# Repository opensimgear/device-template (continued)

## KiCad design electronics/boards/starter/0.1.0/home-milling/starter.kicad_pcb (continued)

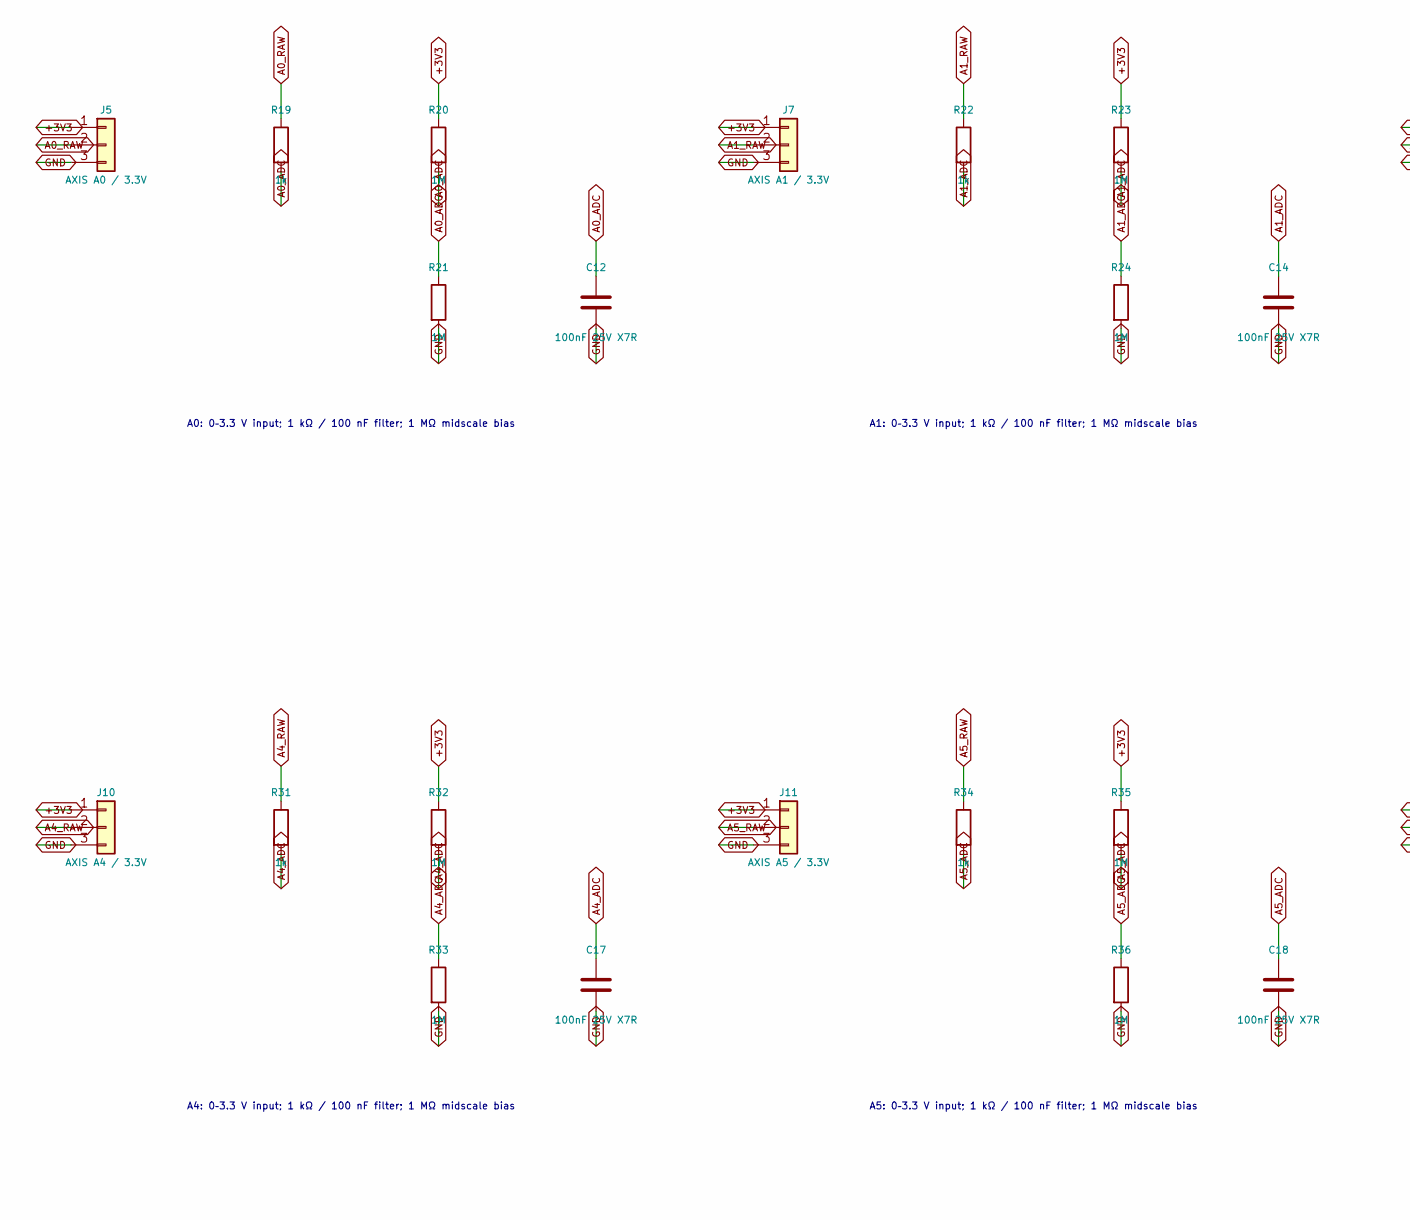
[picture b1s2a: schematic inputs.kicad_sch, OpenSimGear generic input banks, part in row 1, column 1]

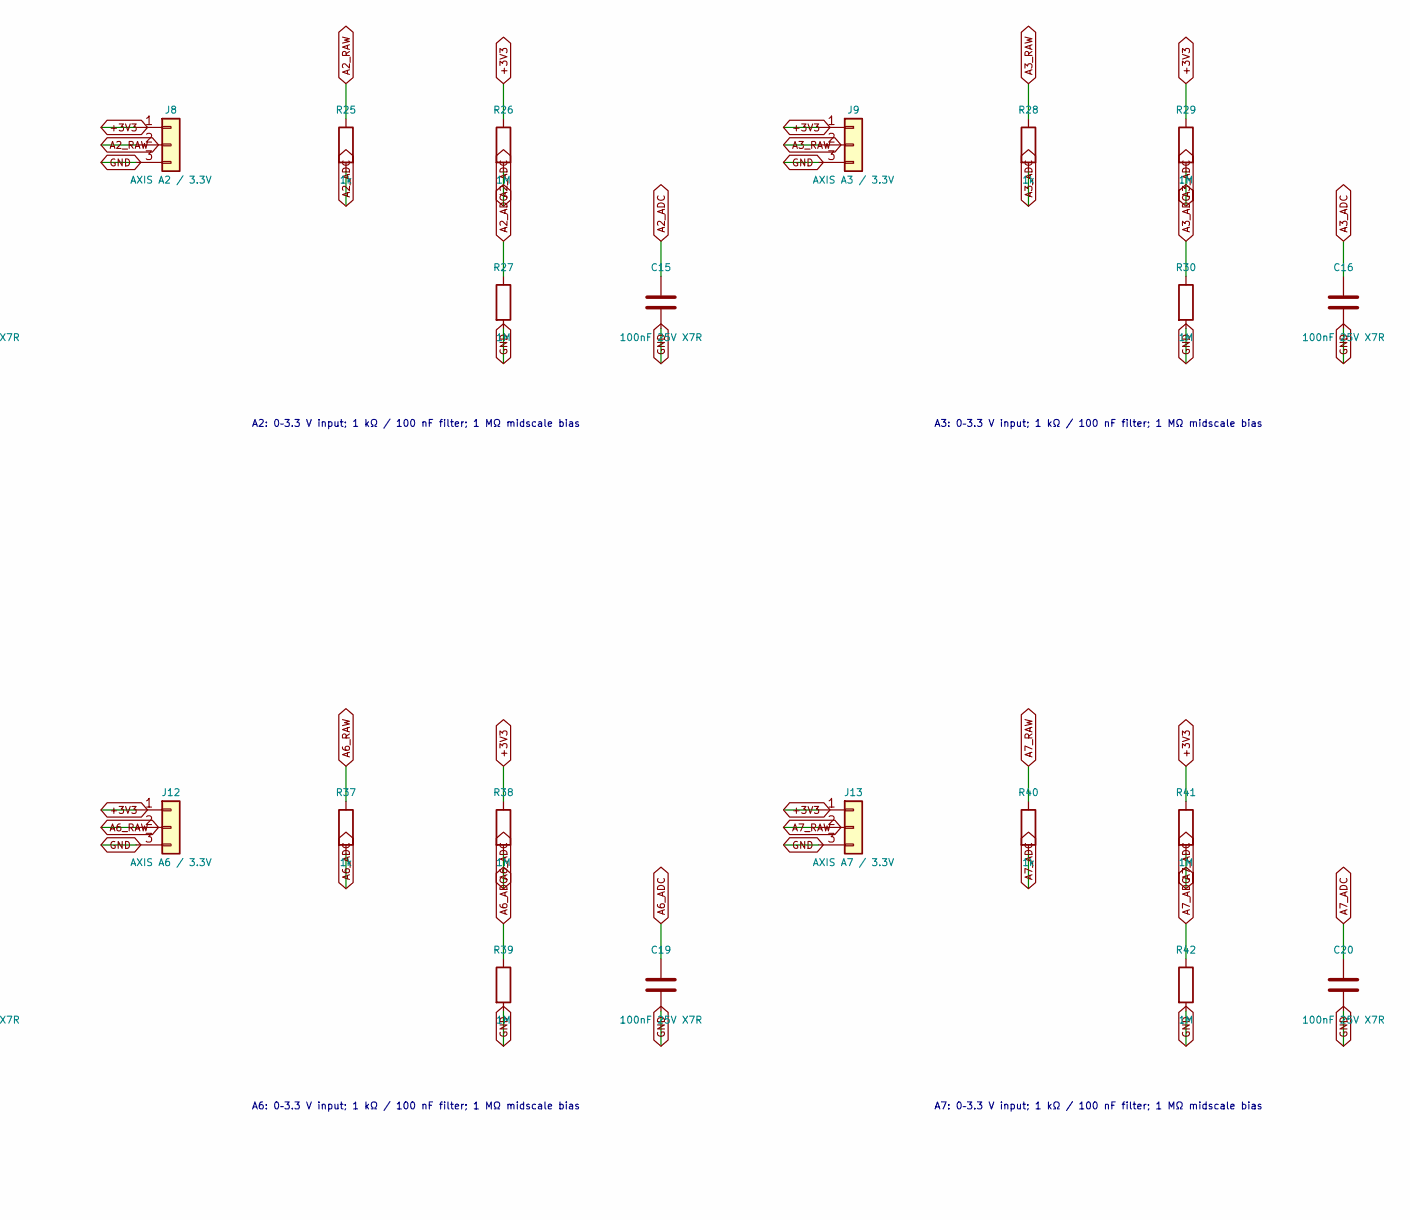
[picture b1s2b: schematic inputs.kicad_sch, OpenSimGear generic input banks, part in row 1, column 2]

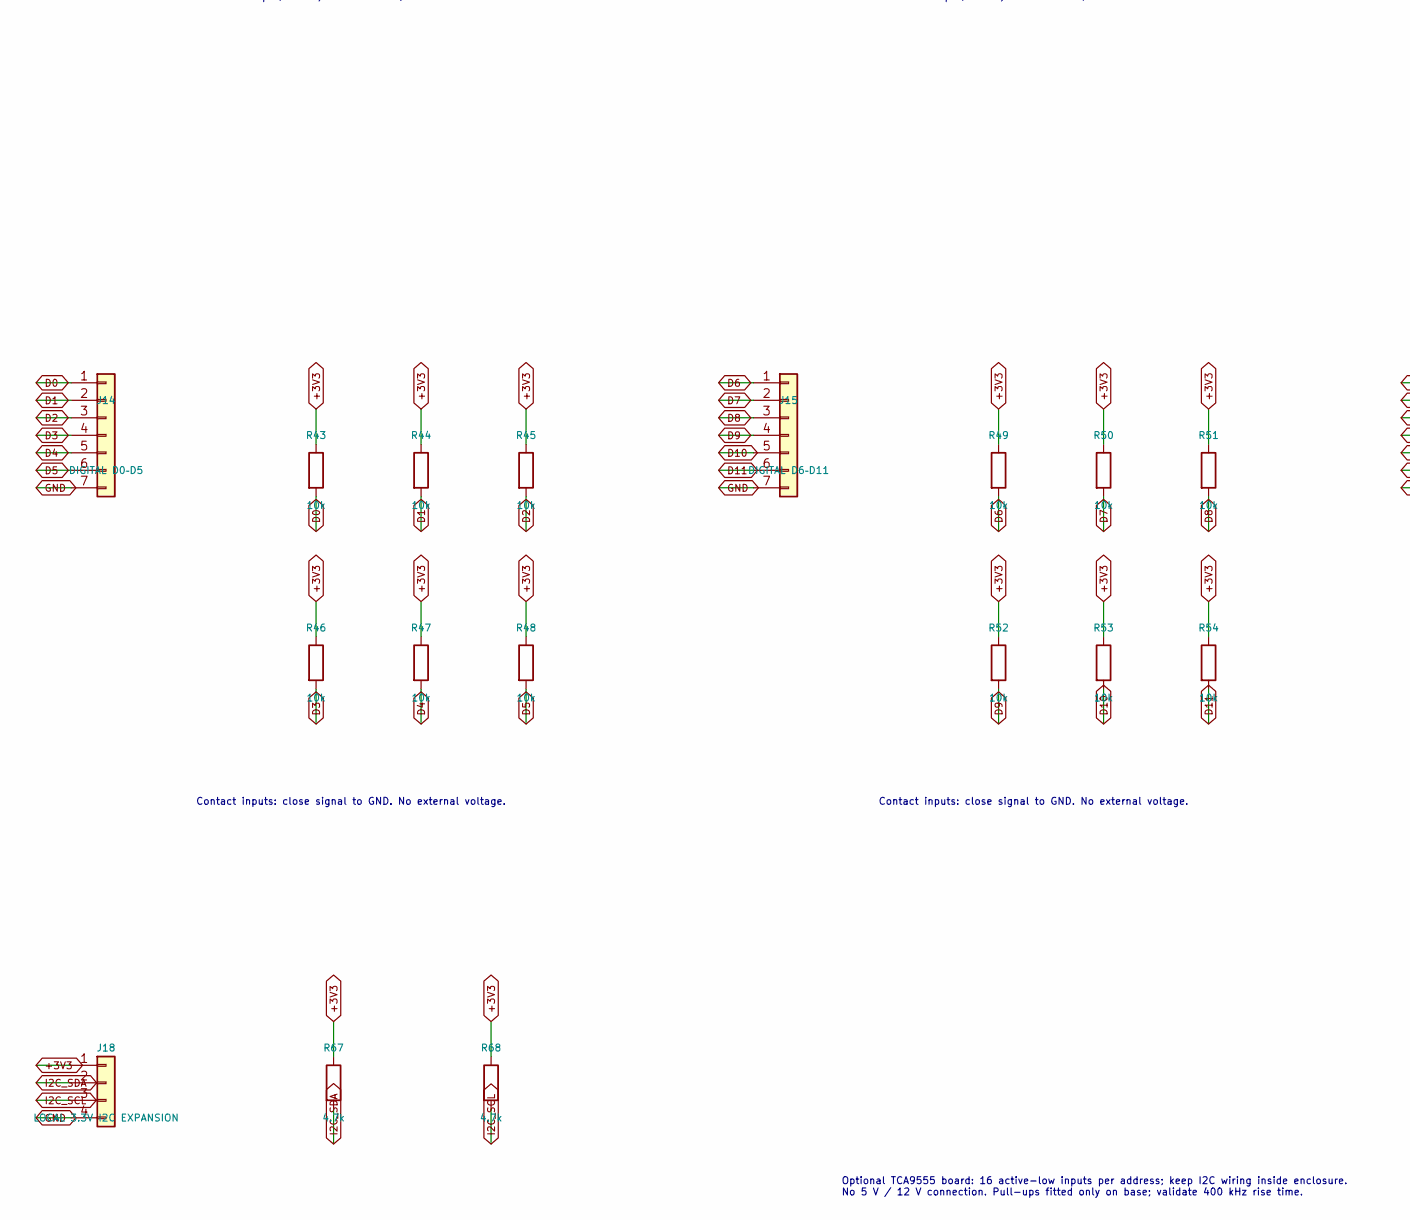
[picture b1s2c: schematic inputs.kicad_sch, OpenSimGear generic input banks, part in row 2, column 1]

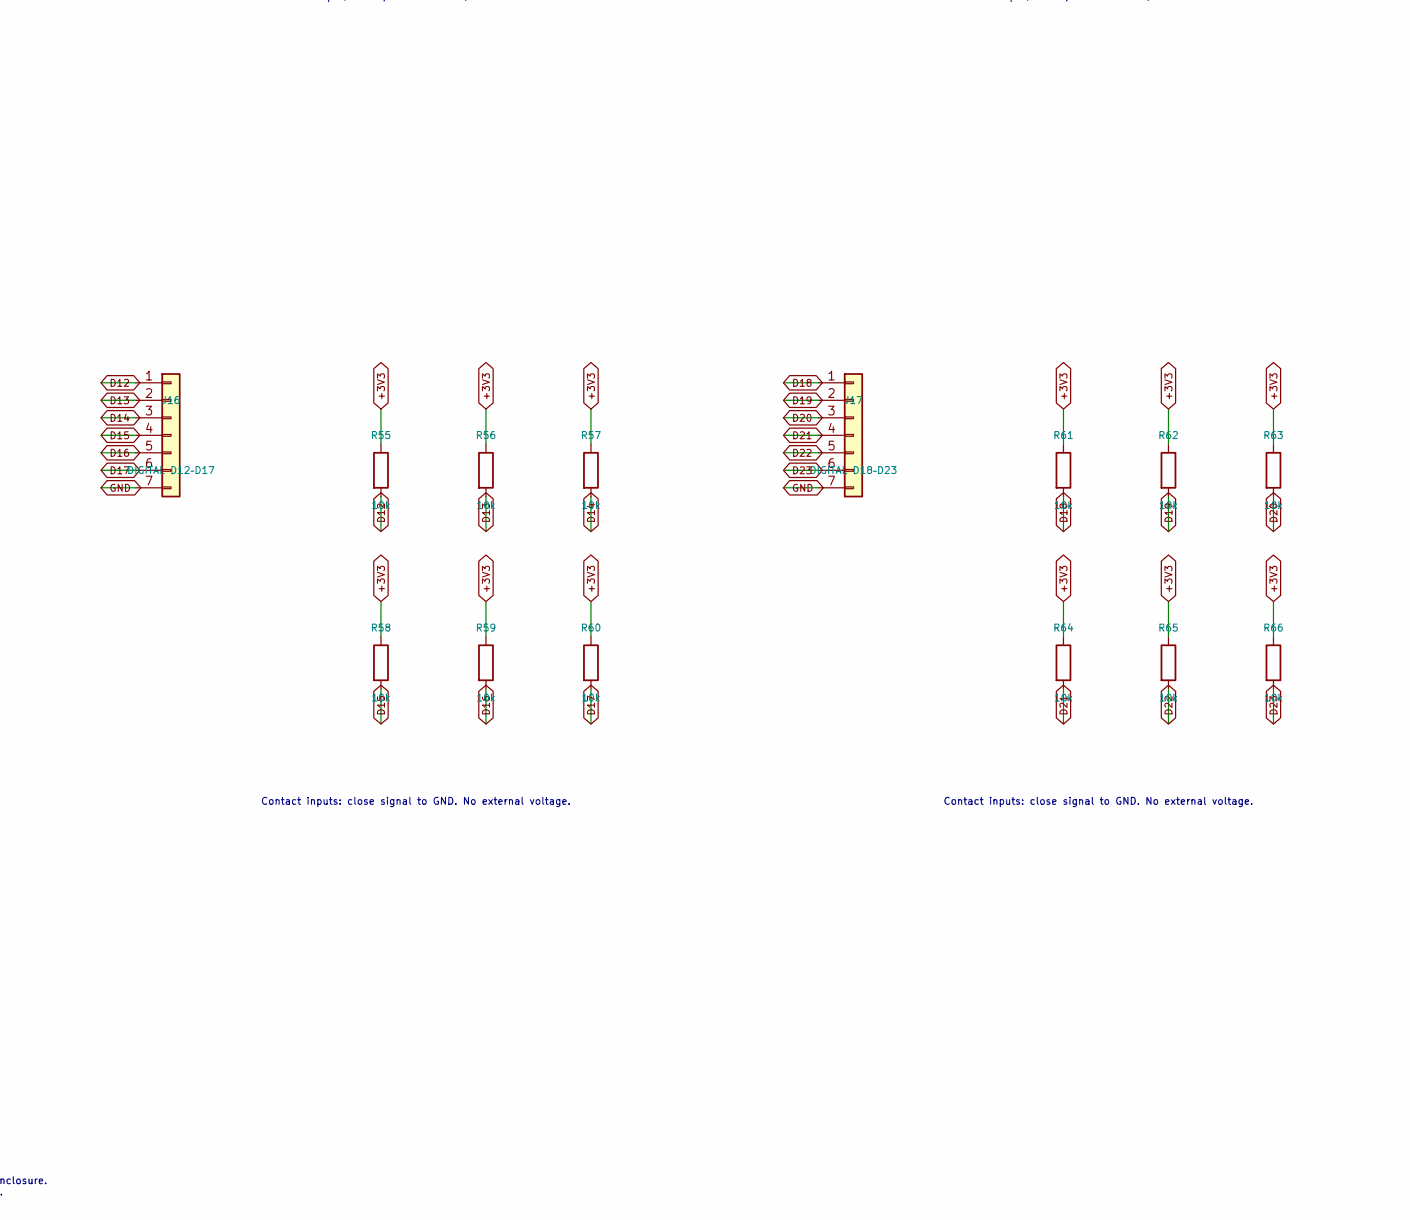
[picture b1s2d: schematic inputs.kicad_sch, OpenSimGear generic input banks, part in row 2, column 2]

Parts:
C12: 100nF 25V X7R; C12_C_0805_2012Metric_HomeMilling; MPN C0805C104K3RACTU
C14: 100nF 25V X7R; C14_C_0805_2012Metric_HomeMilling; MPN C0805C104K3RACTU
C15: 100nF 25V X7R; C15_C_0805_2012Metric_HomeMilling; MPN C0805C104K3RACTU
C16: 100nF 25V X7R; C16_C_0805_2012Metric_HomeMilling; MPN C0805C104K3RACTU
C17: 100nF 25V X7R; C17_C_0805_2012Metric_HomeMilling; MPN C0805C104K3RACTU
C18: 100nF 25V X7R; C18_C_0805_2012Metric_HomeMilling; MPN C0805C104K3RACTU
C19: 100nF 25V X7R; C19_C_0805_2012Metric_HomeMilling; MPN C0805C104K3RACTU
C20: 100nF 25V X7R; C20_C_0805_2012Metric_HomeMilling; MPN C0805C104K3RACTU
J5: AXIS A0 / 3.3V; J5_PinHeader_Samtec_TSW-103-07-L-S_P2.54mm_Vertical_HomeMil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; MPN TSW-103-07-L-S
J7: AXIS A1 / 3.3V; J7_PinHeader_Samtec_TSW-103-07-L-S_P2.54mm_Vertical_HomeMil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; MPN TSW-103-07-L-S
J8: AXIS A2 / 3.3V; J8_PinHeader_Samtec_TSW-103-07-L-S_P2.54mm_Vertical_HomeMil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; MPN TSW-103-07-L-S
J9: AXIS A3 / 3.3V; J9_PinHeader_Samtec_TSW-103-07-L-S_P2.54mm_Vertical_HomeMil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; MPN TSW-103-07-L-S
J10: AXIS A4 / 3.3V; J10_PinHeader_Samtec_TSW-103-07-L-S_P2.54mm_Vertical_HomeMi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; MPN TSW-103-07-L-S
J11: AXIS A5 / 3.3V; J11_PinHeader_Samtec_TSW-103-07-L-S_P2.54mm_Vertical_HomeMi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; MPN TSW-103-07-L-S
J12: AXIS A6 / 3.3V; J12_PinHeader_Samtec_TSW-103-07-L-S_P2.54mm_Vertical_HomeMi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; MPN TSW-103-07-L-S
J13: AXIS A7 / 3.3V; J13_PinHeader_Samtec_TSW-103-07-L-S_P2.54mm_Vertical_HomeMi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; MPN TSW-103-07-L-S
J14: DIGITAL D0–D5; J14_PinHeader_Samtec_TSW-107-07-L-S_P2.54mm_Vertical_HomeMi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; MPN TSW-107-07-L-S
J15: DIGITAL D6–D11; J15_PinHeader_Samtec_TSW-107-07-L-S_P2.54mm_Vertical_HomeMi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; MPN TSW-107-07-L-S
J16: DIGITAL D12–D17; J16_PinHeader_Samtec_TSW-107-07-L-S_P2.54mm_Vertical_HomeMi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; MPN TSW-107-07-L-S
J17: DIGITAL D18–D23; J17_PinHeader_Samtec_TSW-107-07-L-S_P2.54mm_Vertical_HomeMi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; MPN TSW-107-07-L-S
J18: LOCAL 3.3V I2C EXPANSION; J18_PinHeader_Samtec_TSW-104-07-L-S_P2.54mm_Vertical_HomeMi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; MPN TSW-104-07-L-S
R19: 1k; R19_R_0805_2012Metric_HomeMilling; MPN RC0805FR-071KL
R20: 1M; R20_R_0805_2012Metric_HomeMilling; MPN RC0805FR-071ML
R21: 1M; R21_R_0805_2012Metric_HomeMilling; MPN RC0805FR-071ML
R22: 1k; R22_R_0805_2012Metric_HomeMilling; MPN RC0805FR-071KL
R23: 1M; R23_R_0805_2012Metric_HomeMilling; MPN RC0805FR-071ML
R24: 1M; R24_R_0805_2012Metric_HomeMilling; MPN RC0805FR-071ML
R25: 1k; R25_R_0805_2012Metric_HomeMilling; MPN RC0805FR-071KL
R26: 1M; R26_R_0805_2012Metric_HomeMilling; MPN RC0805FR-071ML
R27: 1M; R27_R_0805_2012Metric_HomeMilling; MPN RC0805FR-071ML
R28: 1k; R28_R_0805_2012Metric_HomeMilling; MPN RC0805FR-071KL
R29: 1M; R29_R_0805_2012Metric_HomeMilling; MPN RC0805FR-071ML
R30: 1M; R30_R_0805_2012Metric_HomeMilling; MPN RC0805FR-071ML
R31: 1k; R31_R_0805_2012Metric_HomeMilling; MPN RC0805FR-071KL
R32: 1M; R32_R_0805_2012Metric_HomeMilling; MPN RC0805FR-071ML
R33: 1M; R33_R_0805_2012Metric_HomeMilling; MPN RC0805FR-071ML
R34: 1k; R34_R_0805_2012Metric_HomeMilling; MPN RC0805FR-071KL
R35: 1M; R35_R_0805_2012Metric_HomeMilling; MPN RC0805FR-071ML
R36: 1M; R36_R_0805_2012Metric_HomeMilling; MPN RC0805FR-071ML
R37: 1k; R37_R_0805_2012Metric_HomeMilling; MPN RC0805FR-071KL
R38: 1M; R38_R_0805_2012Metric_HomeMilling; MPN RC0805FR-071ML
R39: 1M; R39_R_0805_2012Metric_HomeMilling; MPN RC0805FR-071ML
R40: 1k; R40_R_0805_2012Metric_HomeMilling; MPN RC0805FR-071KL
R41: 1M; R41_R_0805_2012Metric_HomeMilling; MPN RC0805FR-071ML
R42: 1M; R42_R_0805_2012Metric_HomeMilling; MPN RC0805FR-071ML
R43: 10k; R43_R_0805_2012Metric_HomeMilling; MPN RC0805FR-0710KL
R44: 10k; R44_R_0805_2012Metric_HomeMilling; MPN RC0805FR-0710KL
R45: 10k; R45_R_0805_2012Metric_HomeMilling; MPN RC0805FR-0710KL
R46: 10k; R46_R_0805_2012Metric_HomeMilling; MPN RC0805FR-0710KL
R47: 10k; R47_R_0805_2012Metric_HomeMilling; MPN RC0805FR-0710KL
R48: 10k; R48_R_0805_2012Metric_HomeMilling; MPN RC0805FR-0710KL
R49: 10k; R49_R_0805_2012Metric_HomeMilling; MPN RC0805FR-0710KL
R50: 10k; R50_R_0805_2012Metric_HomeMilling; MPN RC0805FR-0710KL
R51: 10k; R51_R_0805_2012Metric_HomeMilling; MPN RC0805FR-0710KL
R52: 10k; R52_R_0805_2012Metric_HomeMilling; MPN RC0805FR-0710KL
R53: 10k; R53_R_0805_2012Metric_HomeMilling; MPN RC0805FR-0710KL
R54: 10k; R54_R_0805_2012Metric_HomeMilling; MPN RC0805FR-0710KL
R55: 10k; R55_R_0805_2012Metric_HomeMilling; MPN RC0805FR-0710KL
R56: 10k; R56_R_0805_2012Metric_HomeMilling; MPN RC0805FR-0710KL
R57: 10k; R57_R_0805_2012Metric_HomeMilling; MPN RC0805FR-0710KL
R58: 10k; R58_R_0805_2012Metric_HomeMilling; MPN RC0805FR-0710KL
R59: 10k; R59_R_0805_2012Metric_HomeMilling; MPN RC0805FR-0710KL
R60: 10k; R60_R_0805_2012Metric_HomeMilling; MPN RC0805FR-0710KL
R61: 10k; R61_R_0805_2012Metric_HomeMilling; MPN RC0805FR-0710KL
R62: 10k; R62_R_0805_2012Metric_HomeMilling; MPN RC0805FR-0710KL
R63: 10k; R63_R_0805_2012Metric_HomeMilling; MPN RC0805FR-0710KL
R64: 10k; R64_R_0805_2012Metric_HomeMilling; MPN RC0805FR-0710KL
R65: 10k; R65_R_0805_2012Metric_HomeMilling; MPN RC0805FR-0710KL
R66: 10k; R66_R_0805_2012Metric_HomeMilling; MPN RC0805FR-0710KL
R67: 4.7k; R67_R_0805_2012Metric_HomeMilling; MPN RC0805FR-074K7L
R68: 4.7k; R68_R_0805_2012Metric_HomeMilling; MPN RC0805FR-074K7L

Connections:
+3V3: J5.1, J7.1, J8.1, J9.1, J10.1, J11.1, J12.1, J13.1, J18.1, R20.1, R23.1, R26.1, R29.1, R32.1, R35.1, R38.1, R41.1, R43.1, R44.1, R45.1, R46.1, R47.1, R48.1, R49.1, R50.1, R51.1, R52.1, R53.1, R54.1, R55.1, R56.1, R57.1, R58.1, R59.1, R60.1, R61.1, R62.1, R63.1, R64.1, R65.1, R66.1, R67.1, R68.1; also elsewhere on the board
A0_ADC: C12.1, R19.2, R20.2, R21.1; also elsewhere on the board
A0_RAW: J5.2, R19.1
A1_ADC: C14.1, R22.2, R23.2, R24.1; also elsewhere on the board
A1_RAW: J7.2, R22.1
A2_ADC: C15.1, R25.2, R26.2, R27.1; also elsewhere on the board
A2_RAW: J8.2, R25.1
A3_ADC: C16.1, R28.2, R29.2, R30.1; also elsewhere on the board
A3_RAW: J9.2, R28.1
A4_ADC: C17.1, R31.2, R32.2, R33.1; also elsewhere on the board
A4_RAW: J10.2, R31.1
A5_ADC: C18.1, R34.2, R35.2, R36.1; also elsewhere on the board
A5_RAW: J11.2, R34.1
A6_ADC: C19.1, R37.2, R38.2, R39.1; also elsewhere on the board
A6_RAW: J12.2, R37.1
A7_ADC: C20.1, R40.2, R41.2, R42.1; also elsewhere on the board
A7_RAW: J13.2, R40.1
D0: J14.1, R43.2; also elsewhere on the board
D1: J14.2, R44.2; also elsewhere on the board
D2: J14.3, R45.2; also elsewhere on the board
D3: J14.4, R46.2; also elsewhere on the board
D4: J14.5, R47.2; also elsewhere on the board
D5: J14.6, R48.2; also elsewhere on the board
D6: J15.1, R49.2; also elsewhere on the board
D7: J15.2, R50.2; also elsewhere on the board
D8: J15.3, R51.2; also elsewhere on the board
D9: J15.4, R52.2; also elsewhere on the board
D10: J15.5, R53.2; also elsewhere on the board
D11: J15.6, R54.2; also elsewhere on the board
D12: J16.1, R55.2; also elsewhere on the board
D13: J16.2, R56.2; also elsewhere on the board
D14: J16.3, R57.2; also elsewhere on the board
D15: J16.4, R58.2; also elsewhere on the board
D16: J16.5, R59.2; also elsewhere on the board
D17: J16.6, R60.2; also elsewhere on the board
D18: J17.1, R61.2; also elsewhere on the board
D19: J17.2, R62.2; also elsewhere on the board
D20: J17.3, R63.2; also elsewhere on the board
D21: J17.4, R64.2; also elsewhere on the board
D22: J17.5, R65.2; also elsewhere on the board
D23: J17.6, R66.2; also elsewhere on the board
GND: C12.2, C14.2, C15.2, C16.2, C17.2, C18.2, C19.2, C20.2, J5.3, J7.3, J8.3, J9.3, J10.3, J11.3, J12.3, J13.3, J14.7, J15.7, J16.7, J17.7, J18.4, R21.2, R24.2, R27.2, R30.2, R33.2, R36.2, R39.2, R42.2; also elsewhere on the board
I2C_SCL: J18.3, R68.2; also elsewhere on the board
I2C_SDA: J18.2, R67.2; also elsewhere on the board

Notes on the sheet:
A0: 0–3.3 V input; 1 kΩ / 100 nF filter; 1 MΩ midscale bias
A1: 0–3.3 V input; 1 kΩ / 100 nF filter; 1 MΩ midscale bias
A2: 0–3.3 V input; 1 kΩ / 100 nF filter; 1 MΩ midscale bias
A3: 0–3.3 V input; 1 kΩ / 100 nF filter; 1 MΩ midscale bias
A4: 0–3.3 V input; 1 kΩ / 100 nF filter; 1 MΩ midscale bias
A5: 0–3.3 V input; 1 kΩ / 100 nF filter; 1 MΩ midscale bias
A6: 0–3.3 V input; 1 kΩ / 100 nF filter; 1 MΩ midscale bias
A7: 0–3.3 V input; 1 kΩ / 100 nF filter; 1 MΩ midscale bias
Contact inputs: close signal to GND. No external voltage.
Optional TCA9555 board: 16 active-low inputs per address; keep I2C wiring inside enclosure. No 5 V / 12 V connection. Pull-ups fitted only on base; validate 400 kHz rise time.

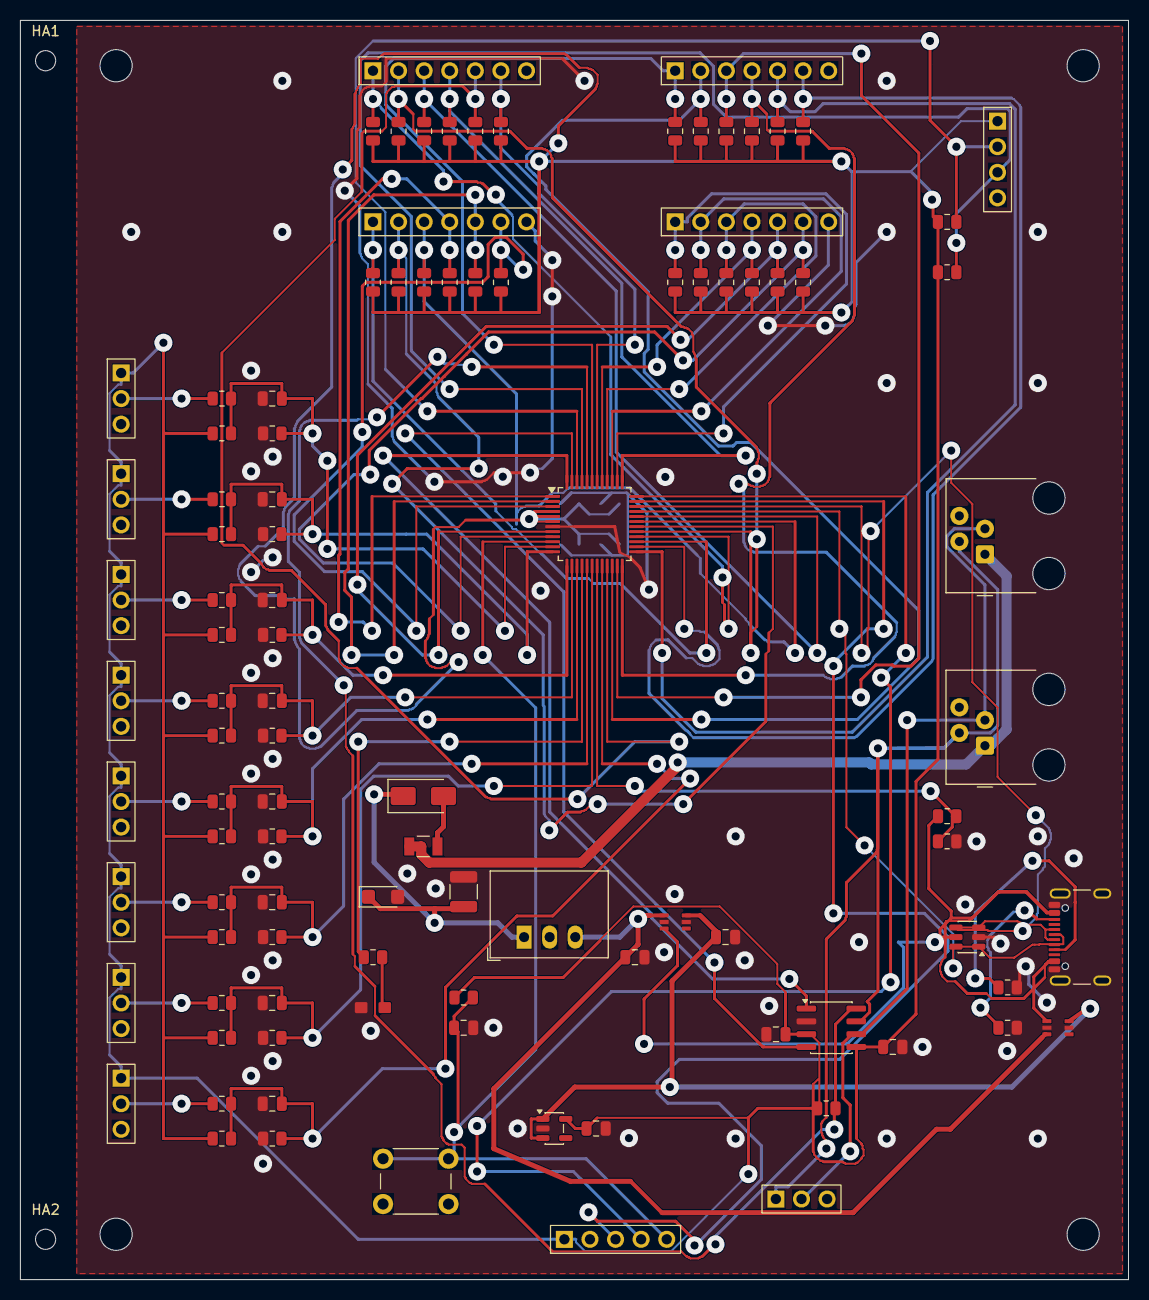
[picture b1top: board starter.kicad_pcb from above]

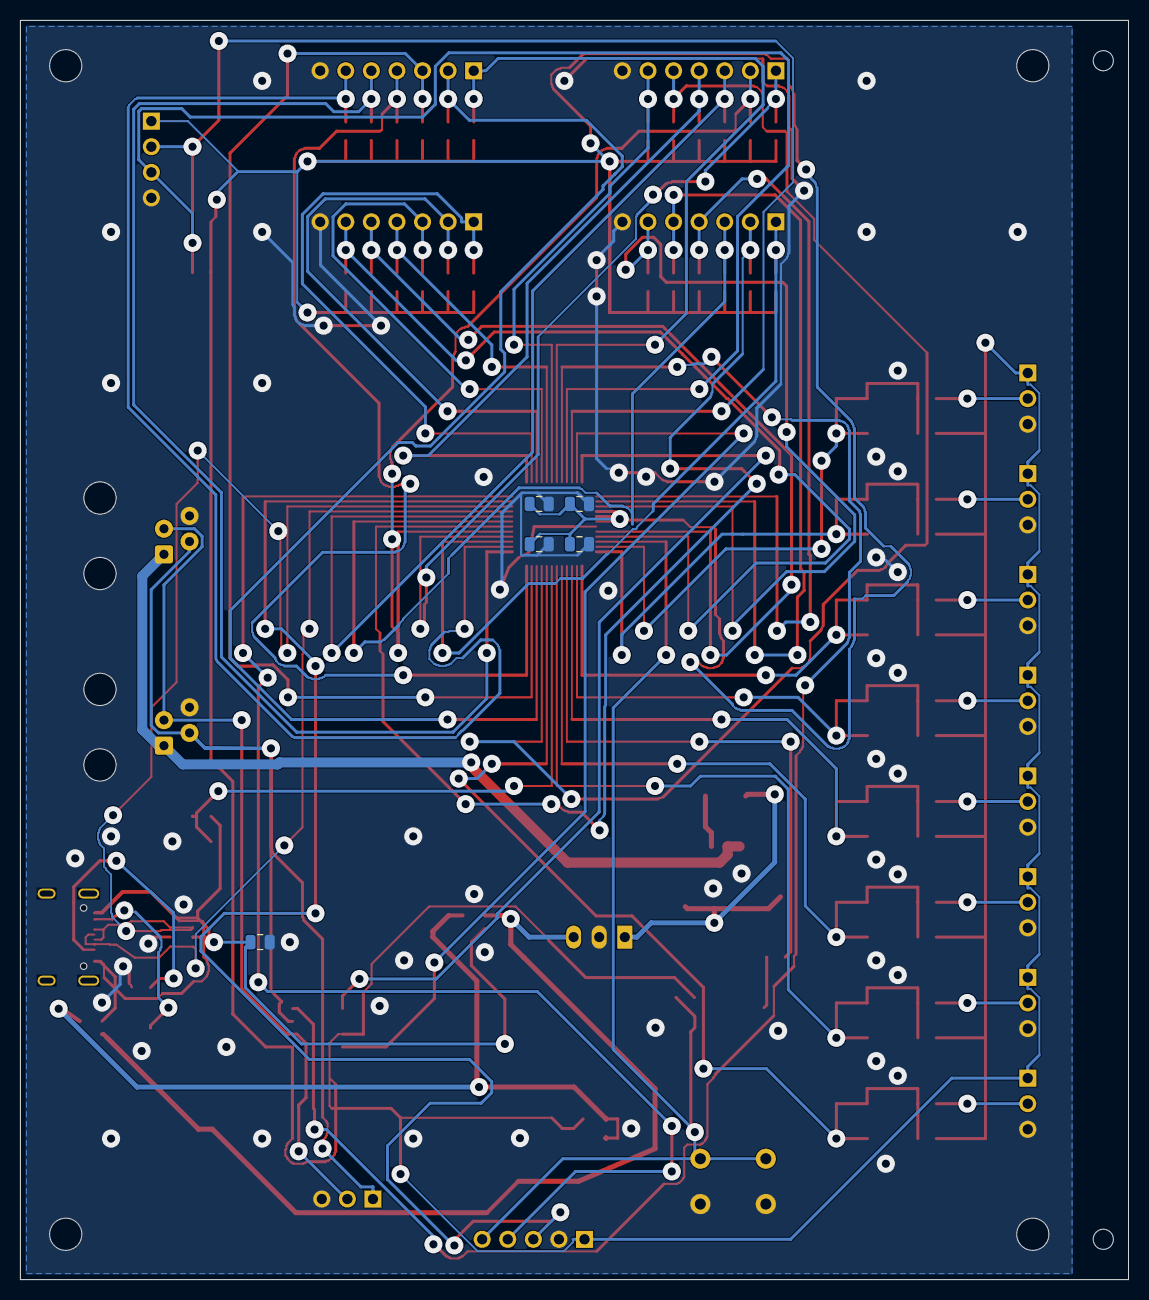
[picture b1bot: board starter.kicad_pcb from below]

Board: 2 copper layers, 110.0 x 125.0 mm, 113 parts (5 on the bottom side), 65 nets.

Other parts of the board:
HA1, HA2: MountingHole_2mm

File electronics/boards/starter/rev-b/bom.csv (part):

Reference,Value,Manufacturer part,Footprint,Datasheet
U1,STM32G0B1CBT6,STM32G0B1CBT6,KiCad:LQFP-48_7x7mm_P0.5mm,https://www.st.com/resource/en/datasheet/stm32g0b1cb.pdf
J1,USB-C DEVICE,USB4105-GF-A,KiCad:USB_C_Receptacle_GCT_USB4105-xx-A_16P_TopMnt_Horizontal,https://gct.co/files/drawings/usb4105.pdf
U2,USBLC6-2SC6,USBLC6-2SC6,KiCad:SOT-23-6,https://www.st.com/resource/en/datasheet/usblc6-2.pdf
R1,5.1k 1%,RC0805FR-075K1L,KiCad:R_0805_2012Metric,https://www.yageogroup.com/component-documentation/download/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
R2,5.1k 1%,RC0805FR-075K1L,KiCad:R_0805_2012Metric,https://www.yageogroup.com/component-documentation/download/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
R3,10k 1%,RC0805FR-0710KL,KiCad:R_0805_2012Metric,https://www.yageogroup.com/component-documentation/download/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
R4,15k 1%,RC0805FR-0715KL,KiCad:R_0805_2012Metric,https://www.yageogroup.com/component-documentation/download/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
U3,TCAN3413D,TCAN3413D,KiCad:SOIC-8_3.9x4.9mm_P1.27mm,https://www.ti.com/lit/ds/symlink/tcan3413.pdf
J2,4P4C POWERED CAN,5301-4P4C,OpenSimGear:RJ4P4C_Evercom_5301-4P4C_Horizontal,https://jlcpcb.com/partdetail/EVERCOM-53014P4C/C3097715
J3,4P4C POWERED CAN,5301-4P4C,OpenSimGear:RJ4P4C_Evercom_5301-4P4C_Horizontal,https://jlcpcb.com/partdetail/EVERCOM-53014P4C/C3097715
R5,10k,RC0805FR-0710KL,KiCad:R_0805_2012Metric,https://www.yageogroup.com/component-documentation/download/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
C1,100nF 25V X7R,C0805C104K3RACTU,KiCad:C_0805_2012Metric,https://content.kemet.com/datasheets/KEM_C1002_X7R_SMD.pdf
J6,CAN TEST / END TERMINATION,TSW-103-07-L-S,OpenSimGear:PinHeader_Samtec_TSW-103-07-L-S_P2.54mm_Vertical,https://suddendocs.samtec.com/prints/tsw-xxx-xx-x-x-xx-xxx-f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
F1,0.25A hold / 24V,1206L025/24YR,OpenSimGear:Fuse_Littelfuse_1206L025-24YR,https://www.littelfuse.com/assetdocs/resettable-ptcs-1206l-d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
D1,SS14,SS14-E3/61T,KiCad:D_SMA,https://www.vishay.com/docs/88746/ss12.pdf
U4,R-78E5.0-0.5,R-78E5.0-0.5,KiCad:Converter_DCDC_RECOM_R-78E-0.5_THT,https://recom-power.com/pdf/Innoline/R-78E-0.5.pdf
U5,TLV75533PDBVR,TLV75533PDBVR,KiCad:SOT-23-5,https://www.ti.com/lit/ds/symlink/tlv755p.pdf
C2,10uF 50V X7R,GRM32ER71H106KA12L,KiCad:C_1210_3225Metric,https://search.murata.co.jp/Ceramy/image/img/A01X/G101/ENG/G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
C3,1uF 25V X7R,C2012X7R1E105K125AB,KiCad:C_0805_2012Metric,https://product.tdk.com/en/search/capacitor/ceramic/mlcc/inf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
C4,1uF 25V X7R,C2012X7R1E105K125AB,KiCad:C_0805_2012Metric,https://product.tdk.com/en/search/capacitor/ceramic/mlcc/inf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
C5,2.2uF 25V X7R,C2012X7R1E225K125AB,KiCad:C_0805_2012Metric,https://product.tdk.com/en/search/capacitor/ceramic/mlcc/inf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
C6,100nF 25V X7R,C0805C104K3RACTU,KiCad:C_0805_2012Metric,https://content.kemet.com/datasheets/KEM_C1002_X7R_SMD.pdf
C7,1uF 25V X7R,C2012X7R1E105K125AB,KiCad:C_0805_2012Metric,https://product.tdk.com/en/search/capacitor/ceramic/mlcc/inf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
C8,100nF 25V X7R,C0805C104K3RACTU,KiCad:C_0805_2012Metric,https://content.kemet.com/datasheets/KEM_C1002_X7R_SMD.pdf
C9,100nF 25V X7R,C0805C104K3RACTU,KiCad:C_0805_2012Metric,https://content.kemet.com/datasheets/KEM_C1002_X7R_SMD.pdf
J4,SWD / 3V3 REFERENCE ONLY,TSW-105-07-L-S,OpenSimGear:PinHeader_Samtec_TSW-105-07-L-S_P2.54mm_Vertical,https://suddendocs.samtec.com/prints/tsw-xxx-xx-x-x-xx-xxx-f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
SW2,RESET,B3F-1002-G,KiCad:SW_PUSH_6mm_H4.3mm,https://omronfs.omron.com/en_US/ecb/products/pdf/en-b3f.pdf
R7,10k,RC0805FR-0710KL,KiCad:R_0805_2012Metric,https://www.yageogroup.com/component-documentation/download/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
C10,100nF 25V X7R,C0805C104K3RACTU,KiCad:C_0805_2012Metric,https://content.kemet.com/datasheets/KEM_C1002_X7R_SMD.pdf
R8,1k,RC0805FR-071KL,KiCad:R_0805_2012Metric,https://www.yageogroup.com/component-documentation/download/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
D4,GREEN,AP2012SGC,OpenSimGear:LED_Kingbright_AP2012SGC_0805,https://www.kingbrightusa.com/images/catalog/SPEC/AP2012SGC.pdf
C11,100nF 25V X7R,C0805C104K3RACTU,KiCad:C_0805_2012Metric,https://content.kemet.com/datasheets/KEM_C1002_X7R_SMD.pdf
U6,LM66100DCKR,LM66100DCKR,OpenSimGear:TI_DCK0006A_SC70-6_LM66100,https://www.ti.com/lit/ds/symlink/lm66100.pdf
U7,LM66100DCKR,LM66100DCKR,OpenSimGear:TI_DCK0006A_SC70-6_LM66100,https://www.ti.com/lit/ds/symlink/lm66100.pdf
D5,SMF15A-E3-08,SMF15A-E3-08,KiCad:D_SMF,https://www.vishay.com/docs/85881/smf5v0atosmf58a.pdf
C13,100nF 25V X7R,C0805C104K3RACTU,KiCad:C_0805_2012Metric,https://content.kemet.com/datasheets/KEM_C1002_X7R_SMD.pdf
J5,AXIS A0 / 3.3V,TSW-103-07-L-S,OpenSimGear:PinHeader_Samtec_TSW-103-07-L-S_P2.54mm_Vertical,https://suddendocs.samtec.com/prints/tsw-xxx-xx-x-x-xx-xxx-f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
R19,1k,RC0805FR-071KL,KiCad:R_0805_2012Metric,https://www.yageogroup.com/component-documentation/download/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
R20,1M,RC0805FR-071ML,KiCad:R_0805_2012Metric,https://www.yageogroup.com/component-documentation/download/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
R21,1M,RC0805FR-071ML,KiCad:R_0805_2012Metric,https://www.yageogroup.com/component-documentation/download/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
C12,100nF 25V X7R,C0805C104K3RACTU,KiCad:C_0805_2012Metric,https://content.kemet.com/datasheets/KEM_C1002_X7R_SMD.pdf
J7,AXIS A1 / 3.3V,TSW-103-07-L-S,OpenSimGear:PinHeader_Samtec_TSW-103-07-L-S_P2.54mm_Vertical,https://suddendocs.samtec.com/prints/tsw-xxx-xx-x-x-xx-xxx-f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
R22,1k,RC0805FR-071KL,KiCad:R_0805_2012Metric,https://www.yageogroup.com/component-documentation/download/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
R23,1M,RC0805FR-071ML,KiCad:R_0805_2012Metric,https://www.yageogroup.com/component-documentation/download/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
R24,1M,RC0805FR-071ML,KiCad:R_0805_2012Metric,https://www.yageogroup.com/component-documentation/download/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
C14,100nF 25V X7R,C0805C104K3RACTU,KiCad:C_0805_2012Metric,https://content.kemet.com/datasheets/KEM_C1002_X7R_SMD.pdf
J8,AXIS A2 / 3.3V,TSW-103-07-L-S,OpenSimGear:PinHeader_Samtec_TSW-103-07-L-S_P2.54mm_Vertical,https://suddendocs.samtec.com/prints/tsw-xxx-xx-x-x-xx-xxx-f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
R25,1k,RC0805FR-071KL,KiCad:R_0805_2012Metric,https://www.yageogroup.com/component-documentation/download/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
R26,1M,RC0805FR-071ML,KiCad:R_0805_2012Metric,https://www.yageogroup.com/component-documentation/download/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
R27,1M,RC0805FR-071ML,KiCad:R_0805_2012Metric,https://www.yageogroup.com/component-documentation/download/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
C15,100nF 25V X7R,C0805C104K3RACTU,KiCad:C_0805_2012Metric,https://content.kemet.com/datasheets/KEM_C1002_X7R_SMD.pdf
J9,AXIS A3 / 3.3V,TSW-103-07-L-S,OpenSimGear:PinHeader_Samtec_TSW-103-07-L-S_P2.54mm_Vertical,https://suddendocs.samtec.com/prints/tsw-xxx-xx-x-x-xx-xxx-f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
R28,1k,RC0805FR-071KL,KiCad:R_0805_2012Metric,https://www.yageogroup.com/component-documentation/download/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
R29,1M,RC0805FR-071ML,KiCad:R_0805_2012Metric,https://www.yageogroup.com/component-documentation/download/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
R30,1M,RC0805FR-071ML,KiCad:R_0805_2012Metric,https://www.yageogroup.com/component-documentation/download/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
C16,100nF 25V X7R,C0805C104K3RACTU,KiCad:C_0805_2012Metric,https://content.kemet.com/datasheets/KEM_C1002_X7R_SMD.pdf
J10,AXIS A4 / 3.3V,TSW-103-07-L-S,OpenSimGear:PinHeader_Samtec_TSW-103-07-L-S_P2.54mm_Vertical,https://suddendocs.samtec.com/prints/tsw-xxx-xx-x-x-xx-xxx-f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
R31,1k,RC0805FR-071KL,KiCad:R_0805_2012Metric,https://www.yageogroup.com/component-documentation/download/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
R32,1M,RC0805FR-071ML,KiCad:R_0805_2012Metric,https://www.yageogroup.com/component-documentation/download/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
R33,1M,RC0805FR-071ML,KiCad:R_0805_2012Metric,https://www.yageogroup.com/component-documentation/download/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
C17,100nF 25V X7R,C0805C104K3RACTU,KiCad:C_0805_2012Metric,https://content.kemet.com/datasheets/KEM_C1002_X7R_SMD.pdf
J11,AXIS A5 / 3.3V,TSW-103-07-L-S,OpenSimGear:PinHeader_Samtec_TSW-103-07-L-S_P2.54mm_Vertical,https://suddendocs.samtec.com/prints/tsw-xxx-xx-x-x-xx-xxx-f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
R34,1k,RC0805FR-071KL,KiCad:R_0805_2012Metric,https://www.yageogroup.com/component-documentation/download/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
R35,1M,RC0805FR-071ML,KiCad:R_0805_2012Metric,https://www.yageogroup.com/component-documentation/download/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
R36,1M,RC0805FR-071ML,KiCad:R_0805_2012Metric,https://www.yageogroup.com/component-documentation/download/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
C18,100nF 25V X7R,C0805C104K3RACTU,KiCad:C_0805_2012Metric,https://content.kemet.com/datasheets/KEM_C1002_X7R_SMD.pdf
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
